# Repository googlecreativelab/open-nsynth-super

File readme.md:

# Open NSynth Super

Open NSynth Super is an experimental physical interface for NSynth, a machine learning algorithm developed by [Google Brain’s Magenta team](https://magenta.tensorflow.org/) to generate new, unique sounds that exist between different sounds. Open NSynth Super allows you to create and explore new sounds that it generates through a simple to use hardware interface that integrates easily into any musician’s production rig. To find out more, visit the [NSynth Super website](https://nsynthsuper.withgoogle.com).

This repository contains all the instructions and files required to build an Open NSynth Super instrument from scratch, and you can use them to make your own version. Anyone can fork the code and schematics to remix the instrument in any way they wish.

### About this document

This document has three chapters – an overview of the instrument itself, a 'make your own' guide, and an overview of the audio creation process.

- [The 'how it works' overview](#how-it-works) summarises the technical and user interface features of the Open NSynth Super instrument.

- [The 'make your own' guide](#guide-how-to-make-open-nsynth-super) takes you through the steps required to build an Open NSynth Super unit and load it with an example Linux image containing pre-computed sample audio, helping you to get started with the instrument straight away.

- [The audio creation overview](#audio-creation-overview) gives a high-level summary of the audio creation pipeline, which enables you to process audio files (on a separate computer) and load the instrument with your own input sounds.

This repository also includes individual chapters on every aspect of Open NSynth Super, so you can build a unit from scratch, or hack and customise any part of it:

- [Application software](/app)
- [Audio creation pipeline](/audio)
- [Case & dials](/case)
- [Firmware & microcontroller](/firmware)
- [OS and provisioning](/linux)
- [PCB and hardware](/pcb_hardware)

# How it works

Open NSynth Super is super simple to integrate into any production music rig. Like many other synthesizer modules, it receives MIDI input via a 5-pin DIN connector, and outputs audio through a 3.5mm jack cable. This simple interface allows it to work with almost any MIDI source, like keyboards, DAWs, or hardware sequencers.

### User interface

The physical interface of Open NSynth Super is constructed around a square touch interface. Using dials in the corners of the touch surface, musicians can select four source sounds and use the touch interface to explore the sounds that the NSynth algorithm has generated between them. In addition, the instrument also has controls for tuning the new sounds via the fine controls.

**(A) Instrument selectors & patch storage** - These rotary dials are used to select the instruments that are assigned to the corners of the interface. In version 1.2.0, these selectors can be pushed down to store or clicked to recall settings patches.

**(B) OLED display** - A high-contrast display shows you the state of the instrument and additional information about the controls that you are interacting with.

**(C) Fine controls** - These six dials are used to further customize the audio output by the device:

- 'Position' sets the initial position of the wave, allowing you to cut out the attack of a waveform, or to start from the tail of a newly created sound.
- 'Attack' controls the time taken for initial run-up of level from nil to peak.
- 'Decay' controls the time taken for the subsequent run down from the attack level to the designated sustain level.
- 'Sustain' sets the level during the main sequence of the sound's duration, until the key is released.
- 'Release' controls the time taken for the level to decay from the sustain level to zero after the key is released.
- 'Volume' adjusts the overall output volume of the device.

**(D) Touch interface** - This is a capacitive sensor, like the mouse pad on a laptop, which is used to explore the world of new sounds that NSynth has generated between your chosen source audio.

### Technical overview

There are several distinct components to each Open NSynth Super unit: a custom PCB with a dedicated microcontroller and firmware for handling user inputs; a Raspberry Pi 3 computer running Raspbian Linux and an openFrameworks-based audio synthesiser application; and a series of scripts for preparing audio on a GPU-equipped Linux server using the NSynth algorithm. In addition to the software, firmware, and hardware, there are files for creating a casing and dials for the unit.

##### Hardware & firmware

The electronics are built around a Raspberry Pi 3 running Raspbian Linux, and a custom PCB used to read the inputs and control the outputs. A microcontroller on the PCB manages the physical inputs: there are four rotary encoders on the four corners for instrument selection; six potentiometers below the interface to control the position, envelope, and volume settings; and a capacitive grid on the surface of the PCB (exposed through the top layer of the case) used to select the mixing point of the four instruments.

More information on the electronics, hardware, and firmware can be found [here](/pcb_hardware), and [here](/firmware). A complete bill of materials for the case and electronics is available in this Excel [spreadsheet](https://storage.googleapis.com/open-nsynth-super/onss_bom_1.2.0.xlsx).

##### Software
Open NSynth Super runs a multisampler audio application built on [openFrameworks](http://openframeworks.cc) to process incoming MIDI note data and generate sound output. More information about this application can be found in the [software readme file](/app).

##### Case
We designed a case for the electronics that can be easily manufactured with a laser cutter, and held together with standard screws and fittings. This design is easily customisable using different materials, colors, dials, and shapes. Read more about this in the [case readme file](/case).

##### Audio
Audio for the Open NSynth Super instrument is produced by the NSynth algorithm. Because generating audio requires a great deal of processing power, this repository includes a set of scripts that you can run on a server which will take any audio recordings of your choice and convert them into a format compatible with the instrument. For more information, see the [audio readme file](/audio) or the [audio creation overview](#audio-creation-overview) in this document.

# Guide: How to make Open NSynth Super

This guide gives you an overview of how to create casing and electronics for Open NSynth Super, and load the device with a premade Linux image which is already set up with application software, hardware support, and example sounds.

The example image file includes the following software features:
- Raspbian Linux Lite
- Full configuration to support the Open NSynth Super mainboard
- Open NSynth Super software application pre-loaded and configured
- Sample audio data
- A read-only filesystem for robustness

You will need the following off-the-shelf items to complete this guide:

- Micro SD card (16GB or 64GB)
- Raspberry Pi 3B+
- 5V 2A micro-USB power supply

You will also need the following Open NSynth Super-specific items, which are detailed in the steps below:

- Open NSynth Super mainboard
- Laser cut Open NSynth Super case
- 3D printed dials (optional)

### 1. Laser cut the shell

This repository contains a reference design for a laser-cut shell for Open NSynth Super. As well as the case design, there are two sizes of 3D-printed dials which can optionally be added to the build. Parts for the case can be cut manually, or obtained easily from a laser-cutting service by supplying these files. More detailed information and specifications for the case can be found in the [case readme](/case) file.

You should make or order a case following the above guide before moving forward with the build. Don't assemble the case yet, as you will need access to the ports on the Raspberry Pi.

### 2. Manufacture and assemble the PCB 

Open NSynth Super is built around a custom PCB with inputs for the hardware controls, audio and data I/O ports, and an OLED display for the UI. The PCB can be ordered fully assembled (this is most cost effective when ordering several boards), or be assembled by hand in a few hours. Further detail on the manufacture and assembly of the board can be found in the [PCB readme](/pcb_hardware) file.

**You will need to obtain or build your PCB before proceeding further with this guide.**

In order to test the board, you will need to have a working Open NSynth Super software installation, which you will prepare at the next step. Before proceeding, connect the Raspberry Pi GPIO pins to the Open NSynth Super mainboard.

### 3. Prepare the SD card

There are two preconfigured OS images available, both loaded with sample audio and fully configured for use with NSynth Super. Depending on the size of your SD card, you can choose either the [64GB image](https://storage.googleapis.com/open-nsynth-super/images/onss_1.2.0_full.img.bz2) or [16GB image](https://storage.googleapis.com/open-nsynth-super/images/onss_1.2.0_lite.img.bz2).

The easiest way to create the SD card is to use GUI software like [Etcher](https://etcher.io/), Win32DiskImager, or the [SD Card Association's](https://www.sdcard.org/downloads/formatter_4/) formatter to burn the example image to a card.

The supplied images are compressed in bz2 format. These can be decompressed on the fly when writing to an SD card using the following command:

```
$ bzcat <IMAGE NAME> | sudo dd of=<DISK NAME>
```

 Connect a keyboard and screen to the Raspberry Pi, insert the SD card, and plug a USB power cable into the socket on the Open NSynth Super mainboard. You should see the Pi booting up on the connected display; when you receive a prompt, you can login with the default username and password: pi / raspberry. **Note that the device might run a file system check when you first boot up from the new card – this will take about 5 minutes depending on the size of the disk.**

### 4. Install the firmware

The firmware will need to be loaded to the microcontroller on your Open NSynth Super mainboard. This allows the software application running on the Raspberry Pi to interact with the controls.

Because the file system is locked for robustness, you will need to remount the disk as read/write by running the following command on your Raspberry Pi:

```
$ sudo mount -o remount,rw /
```

Next, navigate to the firmware directory and run the install command:

```
$ cd /home/pi/open-nsynth-super-master/firmware/src
$ make install
```

This command will build and install the firmware to the microcontroller. You will receive a message on screen confirming the operation has been successful:

```
** Programming Started **
auto erase enabled
Info : device id = 0x10006444
Info : flash size = 32kbytes
wrote 12288 bytes from file ../bin/main.elf in 0.607889s (19.740 KiB/s)
** Programming Finished **
** Verify Started **
verified 11788 bytes in 0.050784s (226.680 KiB/s)
** Verified OK **
** Resetting Target **
adapter speed: 1001 kHz
shutdown command invoked
```

More detailed information about the firmware can be found in the [firmware readme](/firmware) file. When the firmware installation is complete, you can power down the system using the following command, and move to the next step:

```
$ sudo poweroff
```

### 5. Verify the installation

Before assembling the shell and 'finishing' the instrument, it's important to check that everything is functioning correctly. To do this, plug in a MIDI device (like a keyboard), a pair of headphones or speakers, and power on the instrument.

After a few seconds, you should see the grid interface appear on the OLED screen. Move your finger around the touch interface to test its responsiveness. Next, adjust the six controls at the base of the unit; the UI should update according to the control that you are adjusting. Finally, test the four instrument selection encoders, which will scroll through an instrument list on the screen.

To test the audio, ensure your MIDI device is broadcasting on channel 1 (the default channel), and send some notes to the device. You should hear audio coming from the speakers or headphones (if you don't hear anything, make sure the device audio is turned up, and that the envelope and position controls aren't cutting the audible part of the waveform).

Because the standard image is preconfigured, you can use it to test that your Open NSynth Super mainboard is functioning correctly. If all features are up and running, you can move on to final assembly.

### 6. Assemble the shell

Now that you have a fully functioning instrument, you can finally build it into its shell. Power the unit down, remove all connections (e.g. screen, keyboard, MIDI, power), and follow the instructions found [here](/case).

### 7. Play with Open NSynth Super

With the case assembled, firmware installed, and the device tested, you're ready to go and make music with your Open NSynth Super. There are detailed readmes in this repository for the software application, case, PCB and audio creation pipeline if you want to go into more detail, or start hacking the device.

# Audio creation overview

Sounds for Open NSynth Super are created using the neural synthesis technique implemented by Google Brain’s [Magenta](https://magenta.tensorflow.org/) team as part of their NSynth project. You can read more about Magenta and NSynth on their [project page](https://github.com/tensorflow/magenta/tree/master/magenta/models/nsynth).

Because generating audio requires a great deal of processing power, this repository includes a set of scripts that you can run on a server which will take any audio recordings of your choice and convert them into a format compatible with the instrument. This audio pipeline is built on top of the NSynth implementation available through [Magenta's GitHub page](https://github.com/tensorflow/magenta/tree/master/magenta/models/nsynth).

The pipeline has the following stages:

1. Assemble input audio files and assign sounds to corners of the interface
2. Calculate the embeddings of the input sounds with the NSynth model
3. Interpolate between these to create a set of embeddings for newly generated sounds
4. Generate the audio
5. Remove crackles and other artifacts from the generated audio
6. Package and deploy the audio to the device

**More detailed instructions on how to run the pipeline, including how to set up and provision a GPU-equipped Linux server for processing audio, are available [here](/audio).**

---

### Changelog

##### Version 1.2.0
The latest version of Open NSynth Super is 1.2.0. This version adds support for storage and recall of patches and settings, swaps the instrument selector encoders for push-button variants, and introduces note looping to enable sustaining notes beyond their original sample length. Version 1.2.0 software is backwards compatible with version 1.0.0 hardware, although the push-button patch storage feature is not available.

##### Version 1.0.0
Version 1.0.0 is tagged in this repository. The example disk images for software version 1.0.0 are available for download as a [64GB image](https://storage.googleapis.com/open-nsynth-super/images/onss_1.1_full.img) or [16GB image](https://storage.googleapis.com/open-nsynth-super/images/onss_1.0_lite.img).

---

### Notes
This is a collaborative effort between Google Creative Lab and [Magenta](https://github.com/tensorflow/magenta), [Kyle McDonald](https://github.com/kylemcdonald), and our partners at [RRD Labs](https://github.com/dgym). This is not an official Google product.

We encourage open sourcing projects as a way of learning from each other. Please respect our and other creators’ rights, including copyright and trademark rights when present when sharing these works and creating derivative work. If you want more info on Google's policy, you can find it [here](https://www.google.com/permissions/). To contribute to the project, please refer to the [contributing](CONTRIBUTING.md) document in this repository.

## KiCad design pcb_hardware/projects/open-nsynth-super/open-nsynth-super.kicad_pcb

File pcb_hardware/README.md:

# Open NSynth Super PCB hardware

This folder contains all of the source files for making your own Open NSynth Super PCB hardware: a KiCAD project for the PCB in `projects/open-nsynth-super`, rendered gerber files from the KiCAD project in `render/`, and exported schematics from the KiCAD project in `schematics/`.

The PCB design includes a mix of SMT and through-hole components. It is possible to assemble individual boards by hand in a few hours, however for multiple boards it would be advisable to order multiple fully assembled (or at least SMT assembled) PCBs. If you wish to have the PCB manufactured, the files in `render/` should be all you need; additionally, a bill of materials is [available here](https://storage.googleapis.com/open-nsynth-super/onss_bom_1.2.0.xlsx).

For reference, development PCBs were fabricated at the following specification:

- 160mm x 160mm board
- 1.6mm thickness
- 1oz copper
- 2 layers
- Silkscreen both sides
- Smallest drill (for vias) 0.4mm
- Smallest router 0.8mm

# PCB overview

The hardware component of Open NSynth Super provides:

 **(A)** A set of encoders and potentiometers for controlling the audio signal and interface, and a capacitive sensor as a physical interface for controlling the synthesizer voice

 **(B)** Connector for an OLED display module

 **(C)** A dedicated audio output circuit with a 3.5mm audio output

 **(D)** MIDI input via a 5-pin DIN jack

# User inputs

### Rotary encoders

The four instruments are selected by rotary encoders placed in the four corners of the PCB. These are connected to the MCU which keeps track of their changes.

### Potentiometers

The position, sound envelope and volume are controlled by six potentiometers placed along the bottom edge of the PCB. These are connected to the MCU which performs the ADC conversions to read the current values.

### Touch interface

The PCB has a touch sensitive area used to control the interpolation between the four selected instruments. Each axis of the grid is connected to a touch controller IC reading the eleven channels. Because the touch controllers use a fixed I²C address they can not operate on the same bus. For this reason they are not connected to the Raspberry Pi's I²C bus, instead they are connected to the MCU on two additional I²C buses.

# Inputs & outputs

### MIDI

The 5 pin 180 degree MIDI input socket is connected to an opto-isolator circuit. The output of this is connected to the Raspberry Pi's serial input.

### Audio

The PCB includes a good quality DAC driving the line out 3.5mm jack. The DAC is connected to the Raspberry Pi's I²S bus for audio data. It is also connected to the Raspberry Pi's I²C bus for volume and other controls.

The DAC's analog and charge pump sources are supplied by two dedicated LDO voltage regulators for improved sound quality.

# Attaching the display

For ease of assembly the display is an [off the shelf module](https://www.adafruit.com/product/938) with a board to board mounting. It is controlled by I²C and is on the Raspberry Pi bus. The module requires reset logic that can be done in hardware but to reduce component count it is done by GPIO instead. The reset pin is connected to a Raspberry Pi GPIO pin. The OLED screen supports two modes: I²C and SPI. By default, it runs in SPI mode, but for Open NSynth Super it should be set to I²C. On the back of the screen there are two jumper pads (SJ1 and SJ2) that need to be soldered to switch to I²C mode:

The screen module has a through hole connector that connects it directly to the PCB. To improve mechanical resistance, we suggest to solder also the bottom pads. First, apply some flux on the pads:

Apply some solder to the pads:

With the screen PCB held in place (you can use electrical tape to help), push one end of the header through both PCBs and solder to the top side of the main Open NSynth Super board:

Clip the excess header on the reverse side of the board, leaving enough to securely solder to the screen PCB:

Solder the remaining header connector on the screen board (you can cut away any excess header after this step):

Finally, you need to solder the screen on the bottom pads for extra mechanical strength. Put a good amount of flux in the screen PCB hole:

Now, apply a small amount of solder on the tip of the iron, and then, while holding the screen down to the board, hold the iron in the mounting hole for a short period of time (until you feel the solder has melted). Continue holding the board and screen together until you feel that the solder has cooled:

# Finishing the PCB

After soldering the potentiometers and rotary encoders, the pins highlighted below (SW3, RV5, RV4) should be trimmed, to avoid contact with the Raspberry Pi. Optionally, they can also be covered with an insulant material such as electrical tape.

In order to preserve performance of the touch panel, you can add a layer of adhesive plastic to the surface of the board to insulate from moisture (depending on the thickness of the plastic you may wish to adjust the sensitivity of the touch sensor; however the default settings should work for a thin sheet of adhesive plastic.)

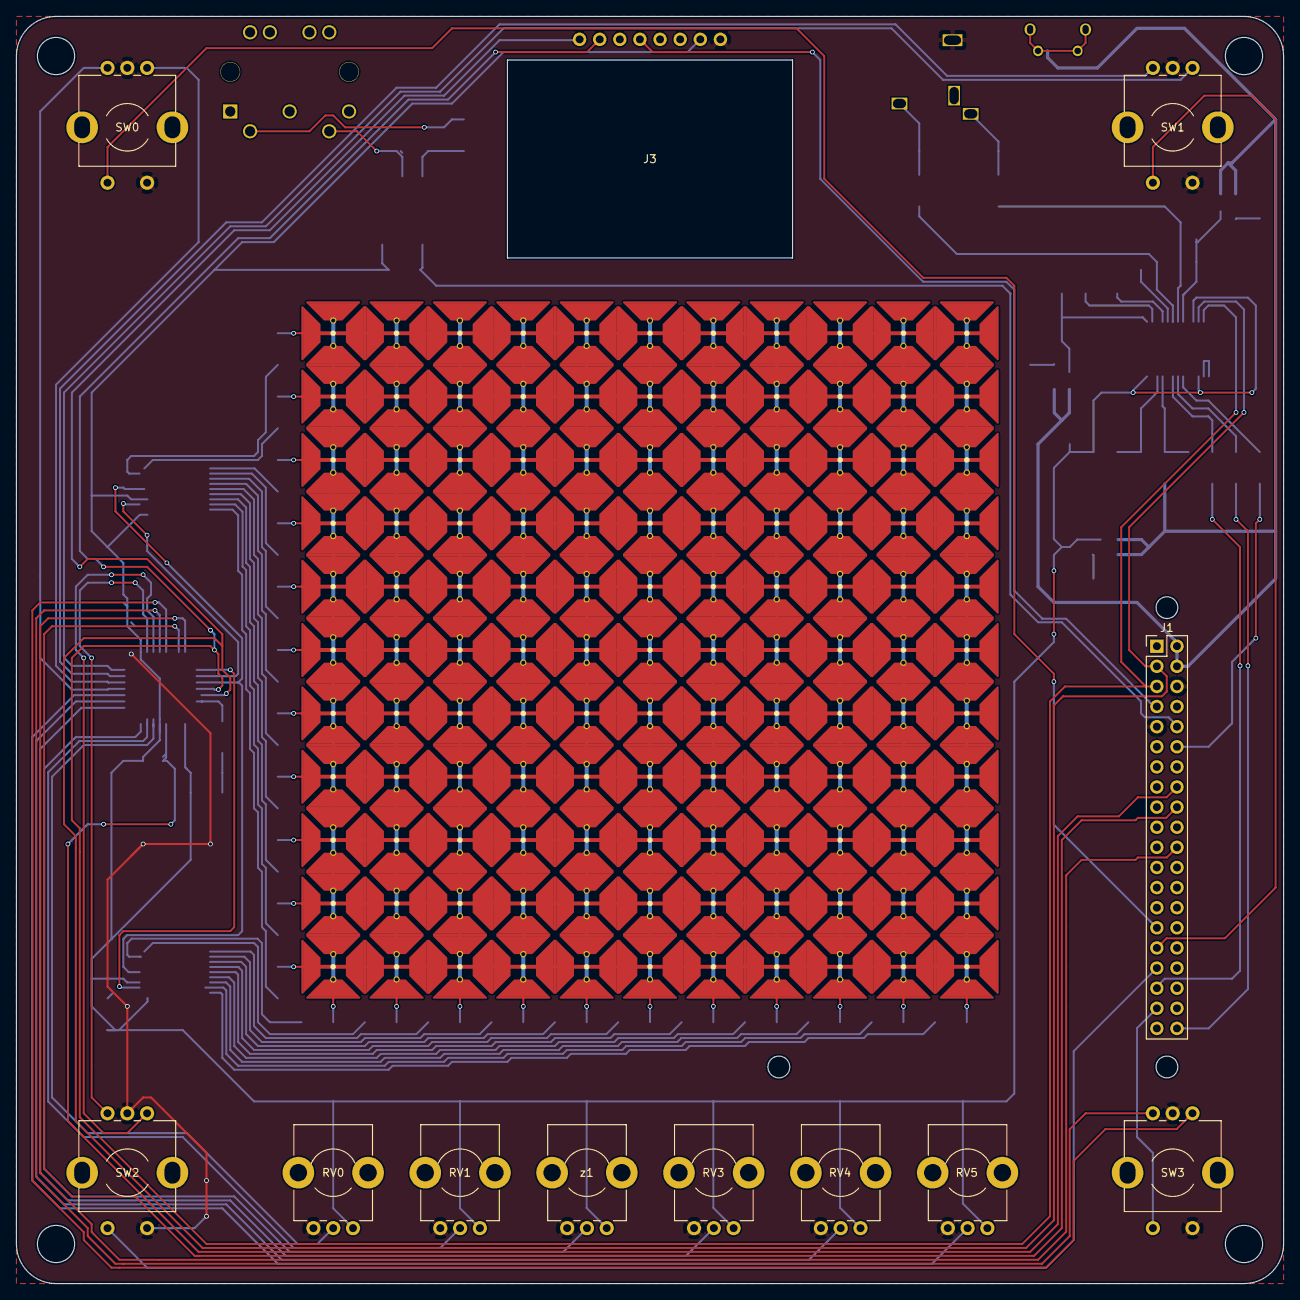
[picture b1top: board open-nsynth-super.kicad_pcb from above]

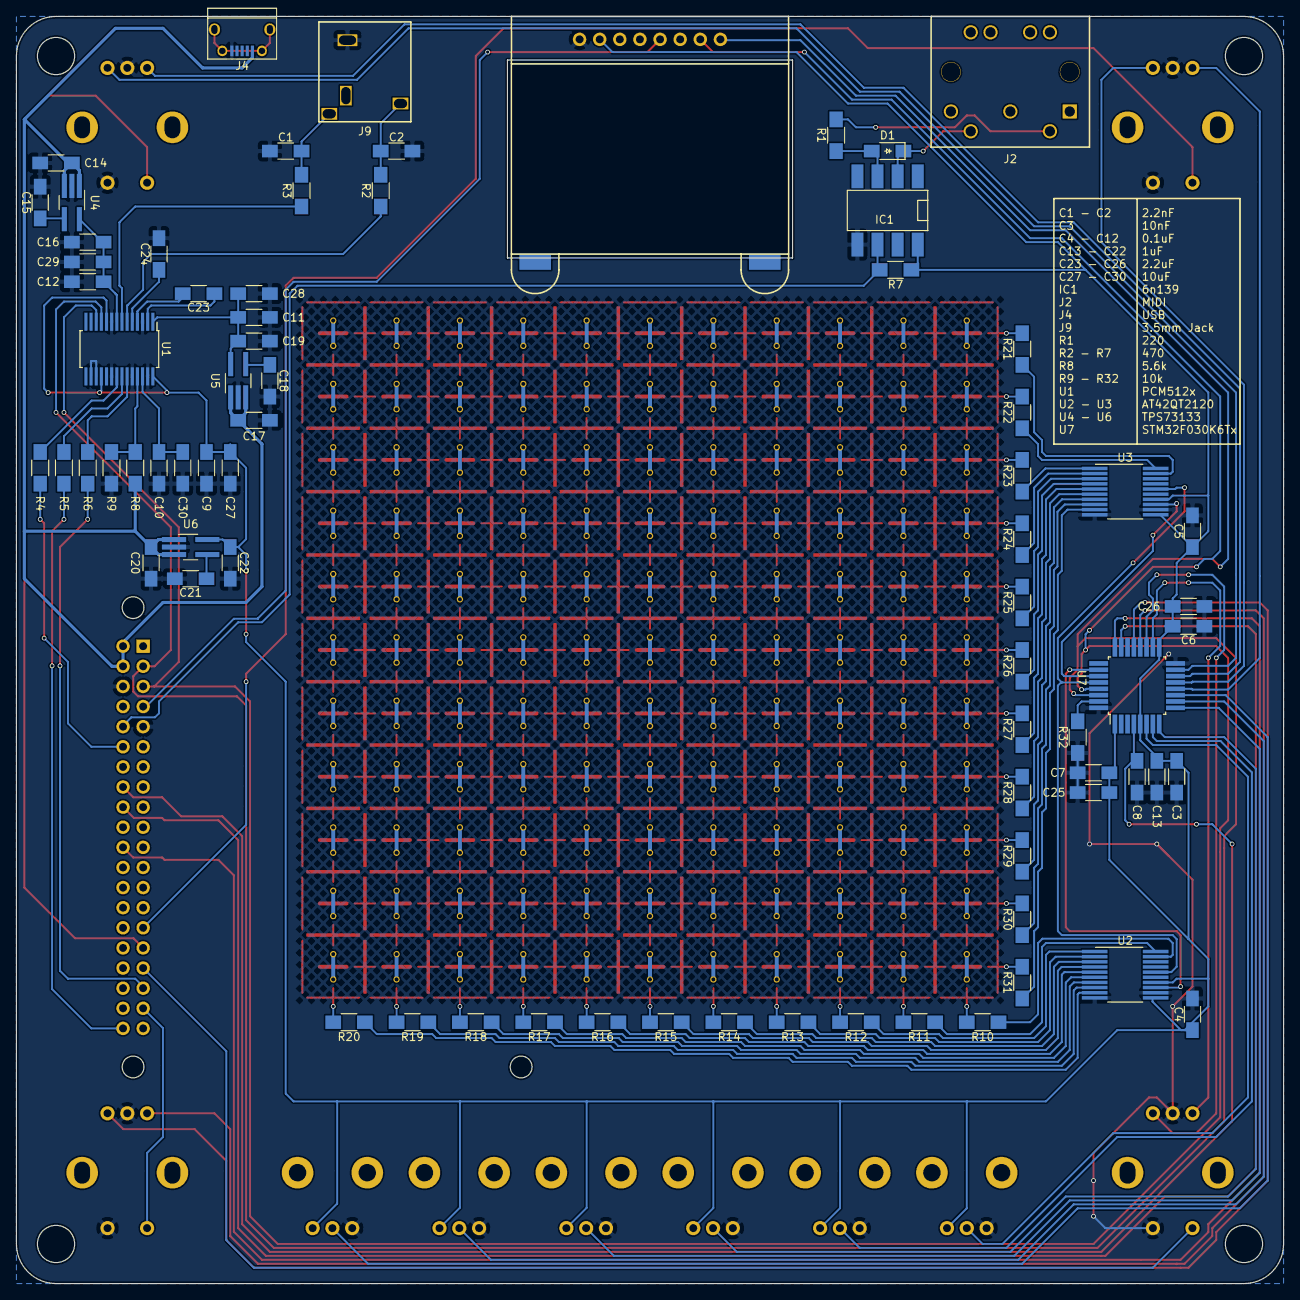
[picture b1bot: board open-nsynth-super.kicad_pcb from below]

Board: 2 copper layers, 160.0 x 160.0 mm, 207 parts (74 on the bottom side), 319 nets.

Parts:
C1, C2: 2.2nF; C_1206_HandSoldering
C3: 0.01uF; C_1206_HandSoldering
C4, C5, C6, C7, C8, C9, C10, C11, C12: 0.1uF; C_1206_HandSoldering
C13, C14, C15, C16, C17, C18, C19, C20, C21, C22: 1uF; C_1206_HandSoldering
C23, C24, C25, C26: 2.2uF; C_1206_HandSoldering
C27, C28, C29, C30: 10uF; C_1206_HandSoldering
D1: DIODE; D_1206
IC1: 6N139; DIP-8_SMD
J1: Raspberry_Pi_2_3; RPi
J2: DIN-5_180degree; MIDI
J3: OLED13; oled13
J4: USB_OTG; USB_Micro-B
J9: Audio-Jack-3; KLBR_4
R1: 220; R_1206_HandSoldering
R2, R3, R4, R5, R6, R7: 470; R_1206_HandSoldering
R8: 5k6; R_1206_HandSoldering
R9, R10, R11, R12, R13, R14, R15, R16, R17, R18, R19, R20, R21, R22, R23, R24, R25, R26, R27, R28, R29, R30, R31, R32: 10k; R_1206_HandSoldering
RV0, RV1, RV3, RV4, RV5: POT; Potentiometer_Alps_RK09K
SW0, SW1, SW2, SW3: Rotary_Encoder; PEC11R-S
TC1, TC2, TC3, TC4, TC5, TC6, TC7, TC8, TC9, TC10, TC11, TC12, TC13, TC14, TC15, TC16, TC17, TC18, TC19, TC20, TC21, TC22, TC23, TC24, TC25, TC26, TC27, TC28, TC29, TC30, TC31, TC32, TC33, TC34, TC35, TC36, TC37, TC38, TC39, TC40, TC41, TC42, TC43, TC44, TC45, TC46, TC47, TC48, TC49, TC50, TC51, TC52, TC53, TC54, TC55, TC56, TC57, TC58, TC59, TC60, TC61, TC62, TC63, TC64, TC65, TC66, TC67, TC68, TC69, TC70, TC71, TC72, TC73, TC74, TC75, TC76, TC77, TC78, TC79, TC80, TC81, TC82, TC83, TC84, TC85, TC86, TC87, TC88, TC89, TC90, TC91, TC92, TC93, TC94, TC95, TC96, TC97, TC98, TC99, TC100, TC101, TC102, TC103, TC104, TC105, TC106, TC107, TC108, TC109, TC110, TC111, TC112, TC113, TC114, TC115, TC116, TC117, TC118, TC119, TC120, TC121: touch; touch_cell
U1: PCM512x; TSSOP-28_4.4x9.7mm_Pitch0.65mm
U2, U3: AT42QT2120; TSSOP-20_4.4x6.5mm_Pitch0.65mm
U4, U5, U6: TPS73133; SOT-23-5
U7: STM32F030K6Tx; LQFP-32_7x7mm_Pitch0.8mm
z1: POT; Potentiometer_Alps_RK09K

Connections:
3.3V_A: C12.1, C16.1, C29.1, U1.8, U4.5
3.3V_C: C11.1, C19.1, C28.1, U1.1, U5.5
3.3V_D: C3.2, C4.1, C5.1, C6.2, C7.2, C9.1, C13.2, C22.1, C25.2, C26.2, C27.1, IC1.8, J3.2, R7.1, RV0.1, RV1.1, RV3.1, RV4.1, RV5.1, U1.10, U1.18, U1.28, U2.11, U2.14, U3.11, U3.14, U6.5, U7.1, U7.5, U7.17, z1.1
5V: C14.1, C17.1, C20.1, J1.2, J1.4, J4.1, R8.1, U4.1, U4.3, U5.1, U5.3, U6.1, U6.3
/MIDI: IC1.6, J1.10, R7.2
/SCL: J1.5, J3.7, U1.12, U7.29
/SDA: J1.3, J3.8, U1.11, U7.30
/audio/BCK: J1.12, R4.2
/audio/DIN: J1.40, R5.2
/audio/LRCL: J1.35, R6.2
/audio/OUTL: C2.1, J9.T, R2.2
/audio/OUTR: C1.1, J9.R, R3.2
/mcu/ICP_CLK: J1.22, U7.24
/mcu/ICP_IO: J1.18, U7.23
/mcu/ICP_RST: C8.2, J1.16, U7.4
/mcu/pot0: RV0.2, U7.6
/mcu/pot1: RV1.2, U7.7
/mcu/pot2: U7.8, z1.2
/mcu/pot3: RV3.2, U7.9
/mcu/pot4: RV4.2, U7.10
/mcu/pot5: RV5.2, U7.11
/mcu/rot0a: SW0.A, U7.12
/mcu/rot0b: SW0.B, U7.13
/mcu/rot1a: SW1.A, U7.14
/mcu/rot1b: SW1.B, U7.15
/mcu/rot2a: SW2.A, U7.18
/mcu/rot2b: SW2.B, U7.19
/mcu/rot3a: SW3.A, U7.20
/mcu/rot3b: SW3.B, U7.21
/mcu/ts0_1_scl: U2.16, U3.16, U7.28
/mcu/ts0_sda: U2.13, U7.26
/mcu/ts1_sda: U3.13, U7.27
/midi/MIDI_4: D1.1, IC1.2, J2.4
/midi/MIDI_5: J2.5, R1.2
GND: C1.2, C2.2, C3.1, C4.2, C5.2, C6.1, C7.1, C8.1, C9.2, C10.2, C11.2, C12.2, C13.1, C14.2, C15.2, C16.2, C17.2, C18.2, C19.2, C20.2, C21.2, C22.2, C24.2, C25.1, C26.1, C27.2, C28.2, C29.2, C30.2, IC1.5, J1.6, J1.9, J3.1, J4.5, J9.S, R9.2, R32.1, RV0.3, RV1.3, RV3.3, RV4.3, RV5.3, SW0.C, SW0.S1, SW1.C, SW1.S1, SW2.C, SW2.S1, SW3.C, SW3.S1, U1.3, U1.9, U1.16, U1.17, U1.20, U1.24, U1.27, U2.10, U2.12, U3.10, U3.12, U4.2, U5.2, U6.2, U7.16, U7.32, z1.3
unnamed: C10.1, C30.1, U1.26
unnamed: C15.1, U4.4
unnamed: C18.1, U5.4
unnamed: C21.1, U6.4
unnamed: C23.1, U1.2
unnamed: C23.2, U1.4
unnamed: C24.1, U1.5
unnamed: D1.2, IC1.3, R1.1
unnamed: J1.7, J3.5
unnamed: R2.1, U1.6
unnamed: R3.1, U1.7
unnamed: R4.1, U1.21
unnamed: R5.1, U1.22
unnamed: R6.1, U1.23
unnamed: R8.2, R9.1, U1.25
unnamed: R10.1, U2.19
unnamed: R10.2, TC1.1
unnamed: R11.1, U2.20
unnamed: R11.2, TC2.1
unnamed: R12.1, U2.1
unnamed: R12.2, TC3.1
unnamed: R13.1, U2.2
unnamed: R13.2, TC4.1
unnamed: R14.1, U2.3
unnamed: R14.2, TC5.1
unnamed: R15.1, U2.4
unnamed: R15.2, TC6.1
unnamed: R16.1, U2.5
unnamed: R16.2, TC7.1
unnamed: R17.1, U2.6
unnamed: R17.2, TC8.1
unnamed: R18.1, U2.7
unnamed: R18.2, TC9.1
unnamed: R19.1, U2.8
unnamed: R19.2, TC10.1
unnamed: R20.1, U2.9
unnamed: R20.2, TC11.1
unnamed: R21.1, U3.19
unnamed: R21.2, TC111.2
unnamed: R22.1, U3.20
unnamed: R22.2, TC100.2
unnamed: R23.1, U3.1
unnamed: R23.2, TC89.2
unnamed: R24.1, U3.2
unnamed: R24.2, TC78.2
unnamed: R25.1, U3.3
unnamed: R25.2, TC67.2
unnamed: R26.1, U3.4
unnamed: R26.2, TC56.2
unnamed: R27.1, U3.5
unnamed: R27.2, TC45.2
unnamed: R28.1, U3.6
unnamed: R28.2, TC34.2
unnamed: R29.1, U3.7
unnamed: R29.2, TC23.2
unnamed: R30.1, U3.8
unnamed: R30.2, TC12.2
unnamed: R31.1, U3.9
unnamed: R31.2, TC1.2
unnamed: R32.2, U7.31
unnamed: TC1.3, TC12.1
unnamed: TC1.4, TC2.2
unnamed: TC2.4, TC3.2
unnamed: TC3.4, TC4.2
unnamed: TC4.4, TC5.2
unnamed: TC5.4, TC6.2
unnamed: TC6.4, TC7.2
unnamed: TC7.4, TC8.2
unnamed: TC8.4, TC9.2
unnamed: TC9.4, TC10.2
unnamed: TC10.3, TC21.1
unnamed: TC10.4, TC11.2
unnamed: TC11.3, TC22.1
unnamed: TC12.3, TC23.1
unnamed: TC12.4, TC13.2
unnamed: TC2.3, TC13.1
unnamed: TC13.3, TC24.1
unnamed: TC13.4, TC14.2
unnamed: TC3.3, TC14.1
unnamed: TC14.3, TC25.1
unnamed: TC14.4, TC15.2
unnamed: TC4.3, TC15.1
unnamed: TC15.3, TC26.1
unnamed: TC15.4, TC16.2
unnamed: TC5.3, TC16.1
unnamed: TC16.3, TC27.1
unnamed: TC16.4, TC17.2
unnamed: TC6.3, TC17.1
unnamed: TC17.3, TC28.1
unnamed: TC17.4, TC18.2
unnamed: TC7.3, TC18.1
unnamed: TC18.3, TC29.1
unnamed: TC18.4, TC19.2
unnamed: TC8.3, TC19.1
unnamed: TC19.3, TC30.1
unnamed: TC19.4, TC20.2
unnamed: TC9.3, TC20.1
unnamed: TC20.3, TC31.1
unnamed: TC20.4, TC21.2
unnamed: TC21.3, TC32.1
unnamed: TC21.4, TC22.2
unnamed: TC22.3, TC33.1
unnamed: TC23.3, TC34.1
unnamed: TC23.4, TC24.2
unnamed: TC24.3, TC35.1
unnamed: TC24.4, TC25.2
unnamed: TC25.3, TC36.1
unnamed: TC25.4, TC26.2
unnamed: TC26.3, TC37.1
unnamed: TC26.4, TC27.2
unnamed: TC27.3, TC38.1
unnamed: TC27.4, TC28.2
unnamed: TC28.3, TC39.1
unnamed: TC28.4, TC29.2
unnamed: TC29.3, TC40.1
unnamed: TC29.4, TC30.2
unnamed: TC30.3, TC41.1
unnamed: TC30.4, TC31.2
unnamed: TC31.3, TC42.1
unnamed: TC31.4, TC32.2
unnamed: TC32.3, TC43.1
unnamed: TC32.4, TC33.2
unnamed: TC33.3, TC44.1
unnamed: TC34.3, TC45.1
unnamed: TC34.4, TC35.2
unnamed: TC35.3, TC46.1
unnamed: TC35.4, TC36.2
unnamed: TC36.3, TC47.1
unnamed: TC36.4, TC37.2
unnamed: TC37.3, TC48.1
unnamed: TC37.4, TC38.2
unnamed: TC38.3, TC49.1
unnamed: TC38.4, TC39.2
unnamed: TC39.3, TC50.1
unnamed: TC39.4, TC40.2
unnamed: TC40.3, TC51.1
unnamed: TC40.4, TC41.2
unnamed: TC41.3, TC52.1
unnamed: TC41.4, TC42.2
unnamed: TC42.3, TC53.1
unnamed: TC42.4, TC43.2
unnamed: TC43.3, TC54.1
unnamed: TC43.4, TC44.2
unnamed: TC44.3, TC55.1
unnamed: TC45.3, TC56.1
unnamed: TC45.4, TC46.2
unnamed: TC46.3, TC57.1
unnamed: TC46.4, TC47.2
unnamed: TC47.3, TC58.1
unnamed: TC47.4, TC48.2
unnamed: TC48.3, TC59.1
unnamed: TC48.4, TC49.2
unnamed: TC49.3, TC60.1
unnamed: TC49.4, TC50.2
unnamed: TC50.3, TC61.1
unnamed: TC50.4, TC51.2
unnamed: TC51.3, TC62.1
unnamed: TC51.4, TC52.2
unnamed: TC52.3, TC63.1
unnamed: TC52.4, TC53.2
unnamed: TC53.3, TC64.1
unnamed: TC53.4, TC54.2
unnamed: TC54.3, TC65.1
unnamed: TC54.4, TC55.2
unnamed: TC55.3, TC66.1
unnamed: TC56.3, TC67.1
unnamed: TC56.4, TC57.2
unnamed: TC57.3, TC68.1
unnamed: TC57.4, TC58.2
unnamed: TC58.3, TC69.1
unnamed: TC58.4, TC59.2
unnamed: TC59.3, TC70.1
unnamed: TC59.4, TC60.2
unnamed: TC60.3, TC71.1
unnamed: TC60.4, TC61.2
unnamed: TC61.3, TC72.1
unnamed: TC61.4, TC62.2
unnamed: TC62.3, TC73.1
unnamed: TC62.4, TC63.2
unnamed: TC63.3, TC74.1
unnamed: TC63.4, TC64.2
unnamed: TC64.3, TC75.1
unnamed: TC64.4, TC65.2
unnamed: TC65.3, TC76.1
unnamed: TC65.4, TC66.2
unnamed: TC66.3, TC77.1
unnamed: TC67.3, TC78.1
unnamed: TC67.4, TC68.2
unnamed: TC68.3, TC79.1
unnamed: TC68.4, TC69.2
unnamed: TC69.3, TC80.1
unnamed: TC69.4, TC70.2
unnamed: TC70.3, TC81.1
unnamed: TC70.4, TC71.2
unnamed: TC71.3, TC82.1
unnamed: TC71.4, TC72.2
unnamed: TC72.3, TC83.1
unnamed: TC72.4, TC73.2
unnamed: TC73.3, TC84.1
unnamed: TC73.4, TC74.2
unnamed: TC74.3, TC85.1
unnamed: TC74.4, TC75.2
unnamed: TC75.3, TC86.1
unnamed: TC75.4, TC76.2
unnamed: TC76.3, TC87.1
unnamed: TC76.4, TC77.2
unnamed: TC77.3, TC88.1
unnamed: TC78.3, TC89.1
unnamed: TC78.4, TC79.2
unnamed: TC79.3, TC90.1
unnamed: TC79.4, TC80.2
unnamed: TC80.3, TC91.1
unnamed: TC80.4, TC81.2
unnamed: TC81.3, TC92.1
unnamed: TC81.4, TC82.2
unnamed: TC82.3, TC93.1
unnamed: TC82.4, TC83.2
unnamed: TC83.3, TC94.1
unnamed: TC83.4, TC84.2
unnamed: TC84.3, TC95.1
unnamed: TC84.4, TC85.2
unnamed: TC85.3, TC96.1
unnamed: TC85.4, TC86.2
unnamed: TC86.3, TC97.1
unnamed: TC86.4, TC87.2
unnamed: TC87.3, TC98.1
unnamed: TC87.4, TC88.2
unnamed: TC88.3, TC99.1
unnamed: TC89.4, TC90.2
unnamed: TC90.4, TC91.2
unnamed: TC91.4, TC92.2
unnamed: TC92.4, TC93.2
unnamed: TC93.4, TC94.2
unnamed: TC94.4, TC95.2
unnamed: TC95.4, TC96.2
unnamed: TC96.4, TC97.2
unnamed: TC97.4, TC98.2
unnamed: TC98.4, TC99.2
unnamed: TC89.3, TC100.1
unnamed: TC100.3, TC111.1
unnamed: TC100.4, TC101.2
unnamed: TC90.3, TC101.1
unnamed: TC101.3, TC112.1
unnamed: TC101.4, TC102.2
unnamed: TC91.3, TC102.1
unnamed: TC102.3, TC113.1
unnamed: TC102.4, TC103.2
unnamed: TC92.3, TC103.1
unnamed: TC103.3, TC114.1
unnamed: TC103.4, TC104.2
unnamed: TC93.3, TC104.1
unnamed: TC104.3, TC115.1
unnamed: TC104.4, TC105.2
unnamed: TC94.3, TC105.1
unnamed: TC105.3, TC116.1
unnamed: TC105.4, TC106.2
unnamed: TC95.3, TC106.1
unnamed: TC106.3, TC117.1
unnamed: TC106.4, TC107.2
unnamed: TC96.3, TC107.1
unnamed: TC107.3, TC118.1
unnamed: TC107.4, TC108.2
unnamed: TC97.3, TC108.1
unnamed: TC108.3, TC119.1
unnamed: TC108.4, TC109.2
unnamed: TC98.3, TC109.1
unnamed: TC109.3, TC120.1
unnamed: TC109.4, TC110.2
unnamed: TC99.3, TC110.1
unnamed: TC110.3, TC121.1
unnamed: TC111.4, TC112.2
unnamed: TC112.4, TC113.2
unnamed: TC113.4, TC114.2
unnamed: TC114.4, TC115.2
unnamed: TC115.4, TC116.2
unnamed: TC116.4, TC117.2
unnamed: TC117.4, TC118.2
unnamed: TC118.4, TC119.2
unnamed: TC119.4, TC120.2
unnamed: TC120.4, TC121.2
rot0s: J1.29, SW0.S2
rot1s: J1.31, SW1.S2
rot2s: J1.33, SW2.S2
rot3s: J1.37, SW3.S2

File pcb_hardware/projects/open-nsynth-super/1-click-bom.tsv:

References	Qty	Description	Manufacturer	MPN	Manufacturer	MPN	Manufacturer	MPN	Manufacturer	MPN	Manufacturer	MPN	Digikey	Mouser	RS	Newark	Farnell
U7	1	stm32f030k6 lqfp32	STMicroelectronics	STM32F030K6T6									497-14046-ND	511STM32F030K6T6	8294644		2432085
U4, U5, U6	3	TPS73133 voltage regulator	Texas Instruments	TPS73133DBVR									296-32553-1-ND	595TPS73133DBVR	6613970	86W6350	2764692
U2, U3	2	AT42QT2120-XU touch sensor ic	Microchip	AT42QT2120-XU									AT42QT2120-XU-ND	556AT42QT2120XU	8996707P	45W2187	2695266
U1	1	PCM512X audio DAC	Texas Instruments	PCM5122PW									296-41605-5-ND	595PCM5122PW	8143732	70W0179	2307931
SW0, SW1, SW2, SW3	4	Rotary Encoder encoder, dual channel, incremental quadrate outputs Potentiometer Alps RK09L Sleve Single Horizontal	Bourns	PEC11R-4315F-N0012									PEC11R-4315F-N0012-ND	652PEC11R4315FN0012			
RV4, RV3, RV2, RV1, RV0, RV5	6	Potentiometer Alps RK09K	Alps	RK09K1130081	BI Technologies	P090S-14T20BR10K							987-1277-ND	688RK09K1130081	7293603	46M2481	1417123
R9, R32, R10, R11, R12, R13, R14, R15, R16, R17, R18, R19, R20, R21, R22, R23, R24, R25, R26, R27, R28, R29, R30, R31	24	Resistor 10k 1206	Vishay	CRCW120610K0FKEA	Panasonic	ERJ-8ENF1002V	Yageo	RC1206FR-0710KL	TE Connectivity	CRG1206F10K			541-10.0KFCT-ND	71CRCW120610KE3	1251192	53K1907	1469970RL
R8	1	Resistor 5k6 1206	TE Connectivity	1623541-1	Vishay	CRCW12065K60FKEA	Panasonic	ERJ-8ENF5601V	KOA Speer	RK73H2BTTD5601F	TE Connectivity	CRG1206F5K6	541-5.60KFCT-ND	660RK73H2BTTD5601F	2232366	28W4437	2139489RL
R2, R3, R4, R5, R6, R7	6	470 ohm 1206 1%	TE Connectivity	CRG1206F470R	Panasonic	ERJ-8ENF4700V	Vishay	CRCW1206470RFKEAHP	Yageo	RC1206FR-07470RL			541-470UDKR-ND	603RC1206FR07470RL	2232215	98K7692	2307726
R1	1	Resistor 220 ohm 1206	TE Connectivity	CRG1206F220R	Panasonic	ERJ-8ENF2200V	Yageo	RC1206FR-07220RL	KOA Speer	RK73H2BTTD2200F			A106073CT-ND	660RK73H2BTTD2200F	2232164	98K7656	2307521
J9	1	Audio-Jack-3 3-pin audio jack receptable (stereo/TRS connector) KLBR 4	Lumberg	KLBR 4	CUI	SJ1-3523N							CP1-3523N-ND	490SJ13523N	5051479	97K2709	1217016
J4	1	USB OTG mini/micro connector Micro-B	FCI	10118194-0001LF	ICC	10118194-0001LF	Amphenol ICC	10118194-0001LF					609-4618-1-ND	649101181940001LF	1370996	67T2260	2668482
J3	1	Adafruit 1.3" OLED display	Adafruit Industries	938									1528-1512-ND	485938			
J2	1	DIN-5 180degree 5-pin DIN connector (5-pin stereo) MIDI	CUI	SDS-50J									CP-2350-ND	490SDS50J	0491087		
J1	1	Raspberry Pi 2 3 expansion header for & RPi	Adafruit Industries	1992									1528-1969-ND	4851992			
IC1	1	6N136 6N139 High Speed Optocoupler, TTL Compatible, CTR 18%, DIP8 DIP-8 SMD	Lite-On	6N139S-L	Lite-On	6N139S							160-1801-ND	8596N139S	6912356		
D1	1	DIODE D 1206	Bourns	CD1206-S01575									CD1206-S01575CT-ND	652CD1206S01575	7734514	09J8040	2211947
C9, C10, C11, C12, C6, C7, C8, C4, C5	9	0.1uF capacitor 1206 X7R	KEMET	C1206C104K5RACTU	Yageo	CC1206KRX7R9BB104							311-1179-6-ND	80C1206C104K5R	6698408	68R4967	718646
C30, C27, C28, C29	4	10uF capacitor 1206 X7R	AVX	1206YC106KAT2A	KEMET	C1206C106K4RACTU	AVX	12063C106KAT2A					478-5725-1-ND	80C1206C106K4R	6983724	96Y8606	1657943
C3	1	0.01uF capacitor 1206 C0G	KEMET	C1206C103J2GACAUTO	KEMET	C1206C103J3GACTU							399-11573-1-ND	80C1206C103J3G	8354024	96Y7238	2426900
C23, C24, C25, C26	4	2.2uF capacitor 1206 X7R	Samsung	CL31B225KBH4PNE	KEMET	C1206X225K5RACTU							399-10086-6-ND	80C1206X225K5R	7661144	53M7334	1414058
C14, C15, C16, C17, C18, C19, C20, C21, C22, C13	10	1uF capacitor 1206 X7R	Yageo	222278115663	AVX	1206YC105KAT2A							478-2576-6-ND	5811206YC105K	6698414	07WX6463	499717
C1, C2	2	2.2nF capacitor 1206 C0G	Vishay	VJ1206A222JXAAT	KEMET	C1206C222J5GACTU							399-8171-6-ND	80C1206C222J5G	6476841	53M7306	1414721

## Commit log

2018-03-13 Initial sync commit
2018-03-14 Make compatible with kitspace.org
2018-03-14 typo dislexia
2018-03-15 Improve BOM with the one linked to from Tindie
    https://www.tindie.com/products/squarofumi/nsynth-super-pcb-googles-ml-synthesizer/
    http://www.digikey.com/short/jj2rt4
2018-03-20 Repo sync commit
2018-03-26 Updating readmes with additional detail
2018-04-04 Updated readmes following Raspberry Pi 3B+ release
2018-04-06 Added a markdown version of the bill of materials
    For those of us without Microsoft Excel. :)
2018-04-13 STL files for a 3D printed case
2018-04-19 Decrease window size to use less screen space
    Removes large black empty rectangle that draws over CLI + X server (if installed).
2018-04-21 Created server code to replace the i2c interface for receiving interpolation values for the instruments
2018-04-21 Referenced socket implmentation
2018-04-21 Linked ofApp to InsturmentServer
2018-05-21 initial release for rpi 3 b+ and openframeworks from git
2018-05-21 Include firmeware install
2018-05-21 some troubleshooting
2018-05-21 Add usb-midi as input
2018-05-23 Fixed opencd and openframeworks setup
2018-05-28 Extend the supported range of midi messages. Done by jditte
2018-05-28 Fix #43 by filtering out system real-time messages
2018-06-23 update linux/nsynth-setup.sh
    due to the change of openFrameworks download URL to https.
2018-07-30 Filtered out all system real-time messages
2018-08-10 Added openFrameworks 0.10.0 support
2018-08-10 Added Raspberry Pi 3B+ support
2018-08-10 Add note looping support
2018-08-10 Add patch saving and loading
2018-08-10 Add encoder switches to use for patches
2019-01-04 Updates to readme files
2019-01-04 Updates to main readme
2019-01-15 Add support for MIDI running status. Add support for zero velocity note-off.
2019-01-15 Adding references to midi specification in comments.
2019-01-15 Adding support for running status
2021-02-17 Update schematics for Kicad 5
